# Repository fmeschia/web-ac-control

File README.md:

This repository contains the sources for a system to control a
Whynter ARC-110D portable air conditioner unit via the web, through
Raspberry Pi and Arduino hardware.

Unless otherwise specified, the following license applies to all files:

Licensed under the Apache License, Version 2.0 (the "License");
you may not use this file except in compliance with the License.
You may obtain a copy of the License at

    http://www.apache.org/licenses/LICENSE-2.0

Unless required by applicable law or agreed to in writing, software
distributed under the License is distributed on an "AS IS" BASIS,
WITHOUT WARRANTIES OR CONDITIONS OF ANY KIND, either express or implied.
See the License for the specific language governing permissions and
limitations under the License.

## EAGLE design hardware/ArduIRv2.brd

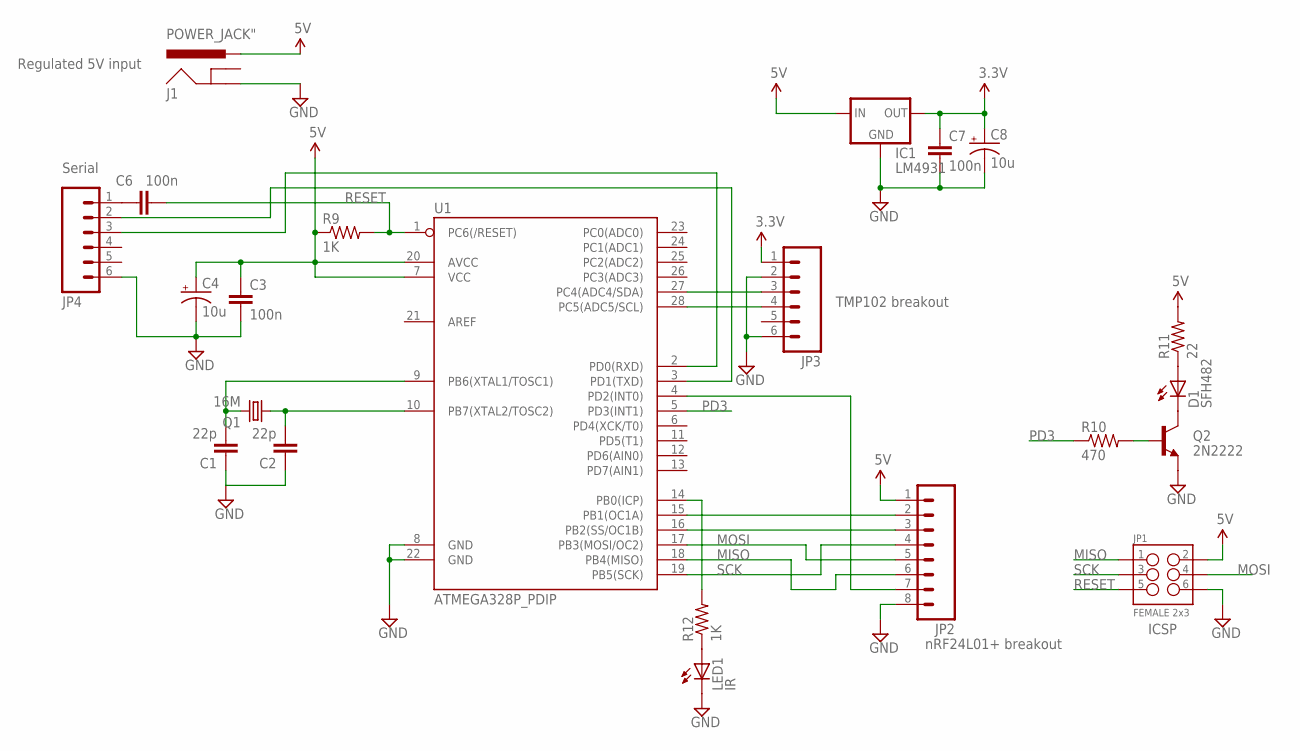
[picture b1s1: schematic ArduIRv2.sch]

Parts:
C1, C2: 22p; CAP-PTH-SMALL
C3, C6, C7: 100n; CAP-PTH-SMALL-KIT
C4, C8: 10u; CPOL-RADIAL-10UF-25V
D1: SFH482
IC1: LM4931; L4931_REGULATOR
J1: POWER_JACK"; POWER_JACK
JP1: FEMALE 2x3; 2X3-SHROUDED
JP2: M08SILK_FEMALE_PTH; 1X08
JP3, JP4: M06SILK_FEMALE_PTH; 1X06
LED1: IR; LED5MM
Q1: 16M; HC49US
Q2: 2N2222; TO-92-AMMO
R9, R12: 1K; AXIAL-0.1EZ
R10: 470; AXIAL-0.1EZ
R11: 22; AXIAL-0.1EZ
U1: ATMEGA328P_PDIP; DIL28-3

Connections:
3.3V: C7.1, C8.1 (+), IC1.OUT, JP3.1
5V: C3.1, C4.1 (+), IC1.IN, J1.PWR, JP1.2, JP2.1, R9.P$1 (1), R11.P$2 (2), U1.7 (VCC), U1.20 (AVCC)
GND: C1.1, C2.1, C3.2, C4.2 (-), C7.2, C8.2 (-), IC1.GND, J1.GND, JP1.6, JP2.8, JP3.2, JP3.6, JP4.6, LED1.K (C), Q2.1 (E), U1.8 (GND), U1.22 (GND)
MISO: JP1.1, JP2.6, U1.18 (PB4(MISO))
MOSI: JP1.4, JP2.5, U1.17 (PB3(MOSI/OC2))
unnamed: JP2.2, U1.15 (PB1(OC1A))
unnamed: JP2.3, U1.16 (PB2(SS/OC1B))
unnamed: R12.P$2 (2), U1.14 (PB0(ICP))
unnamed: JP2.7, U1.4 (PD2(INT0))
unnamed: C1.2, Q1.2, U1.9 (PB6(XTAL1/TOSC1))
unnamed: C2.2, Q1.1, U1.10 (PB7(XTAL2/TOSC2))
unnamed: JP3.3, U1.27 (PC4(ADC4/SDA))
unnamed: JP3.4, U1.28 (PC5(ADC5/SCL))
unnamed: Q2.2 (B), R10.P$2 (2)
unnamed: D1.K (C), Q2.3 (C)
unnamed: D1.A, R11.P$1 (1)
unnamed: LED1.A, R12.P$1 (1)
unnamed: C6.2, JP4.1
unnamed: JP4.2, U1.3 (PD1(TXD))
unnamed: JP4.3, U1.2 (PD0(RXD))
PD3: R10.P$1 (1), U1.5 (PD3(INT1))
RESET: C6.1, JP1.5, R9.P$2 (2), U1.1 (PC6(/RESET))
SCK: JP1.3, JP2.4, U1.19 (PB5(SCK))

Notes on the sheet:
Regulated 5V input
TMP102 breakout
nRF24L01+ breakout
ICSP
Serial

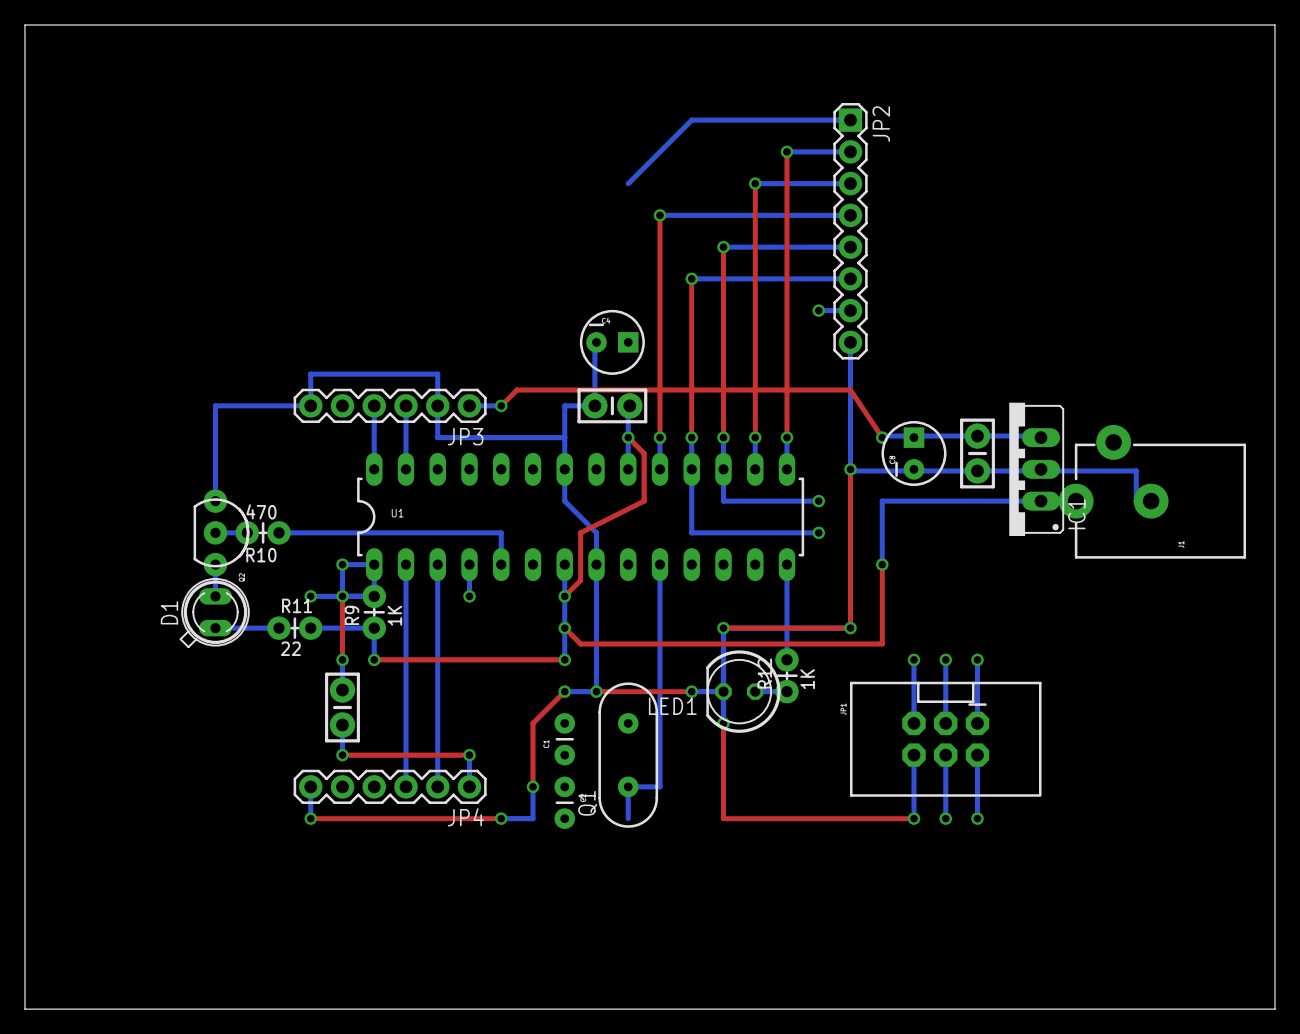
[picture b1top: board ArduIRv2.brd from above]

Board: 2 copper layers, 100.0 x 78.7 mm, 22 parts (0 on the bottom side), 23 nets.

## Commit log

2015-01-22 Added reverse engineering of IR protocol and Arduino source
2015-01-23 Use one-shot conversion with TMP102
2015-01-23 Various reworks RPi-side
2015-01-24 Comments in the nRF2401 code
2015-01-24 Different temperature readout system
2015-01-24 Changed addresses and padded response to 5 bytes
2015-01-24 Changed RF2401A addresses and padded response to 6 bytes
2015-01-26 Updated RPi for nRF24L01+
2015-01-26 Updated Arduino for nRF24L01+
2015-01-26 Changes in RPi for nRF24L01+
2015-01-27 Update ardu-temp.cpp
    Made sure that radio is not in listening mode while write() is invoked
2015-01-27 Fixed SQL in readtemp.js
2015-01-27 Blink temperature when readout is requested
2015-01-27 Reverse engineering of checksum
2015-01-29 More reverse engineering
2015-01-29 Reverted to 24-hour chart
2015-02-02 Added rolling code to IR commands
2015-02-02 Added rolling code RPi-side
2015-02-02 Added rolling code RPi side
2015-02-03 Source code beauty treatment
2015-02-07 Added comments to Arduino source code
2015-02-07 Changed IR codes for FAN 1 74 F
2015-02-09 Changed logic to recognize "A/C ON" on Arduino
2015-05-31 Code cleaning
2015-05-31 Comments added
2015-06-27 Minor change to Arduino code
2015-07-14 Documentation changes
2015-07-22 Added hardware files and Apache license
2015-07-25 Version for nRF2401A radio PTX
2015-07-27 Arduino software changed for nRF2401A
2015-07-27 Various change for nRF2401A
2015-07-28 Changed to 48-hour chart, and disabled purge after 7 days
2015-07-29 Added README file to compile native ardu-* programs
2015-07-30 Better power usage with sleep + wake on IRQ from radio and serial
2015-07-31 Refactored to avoid use of PCIntLib
2015-07-31 Replaced wrong EAGLE schematic with right one
2015-07-31 Changed for more comfortable temperature
2015-08-07 Improved handling of sleep timeout
2015-08-09 Added makefile for c++ programs
2015-08-21 Minor changes
2016-06-11 Added database DDL, added temp table purge and history log

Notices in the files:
parts and their libraries:
SparkFun-Capacitors: Licensing: Creative Commons ShareAlike 4.0 International - https://creativecommons.org/licenses/by-sa/4.0
